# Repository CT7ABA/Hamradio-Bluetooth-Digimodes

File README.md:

# Bluetooth-Digimodes With BT401
Hamradio Digital Modes without Cables.

Don't forget to set up the BT401 to the right communication velocity of your Rig

AT+CT01\r\n for 9600 Baud 

AT+CT02\r\n for 19200 Baud 

AT+CT03\r\n for 38400 Baud

AT+CT04\r\n for 57600 Baud

AT+CT05\r\n for 115200 Baud etc.... take a look at the BT401 manual for more information.

Project still in progress, PCB allready tested. RV1 & RV2 still not the correct values, for the FT-817 both RV are bypassed

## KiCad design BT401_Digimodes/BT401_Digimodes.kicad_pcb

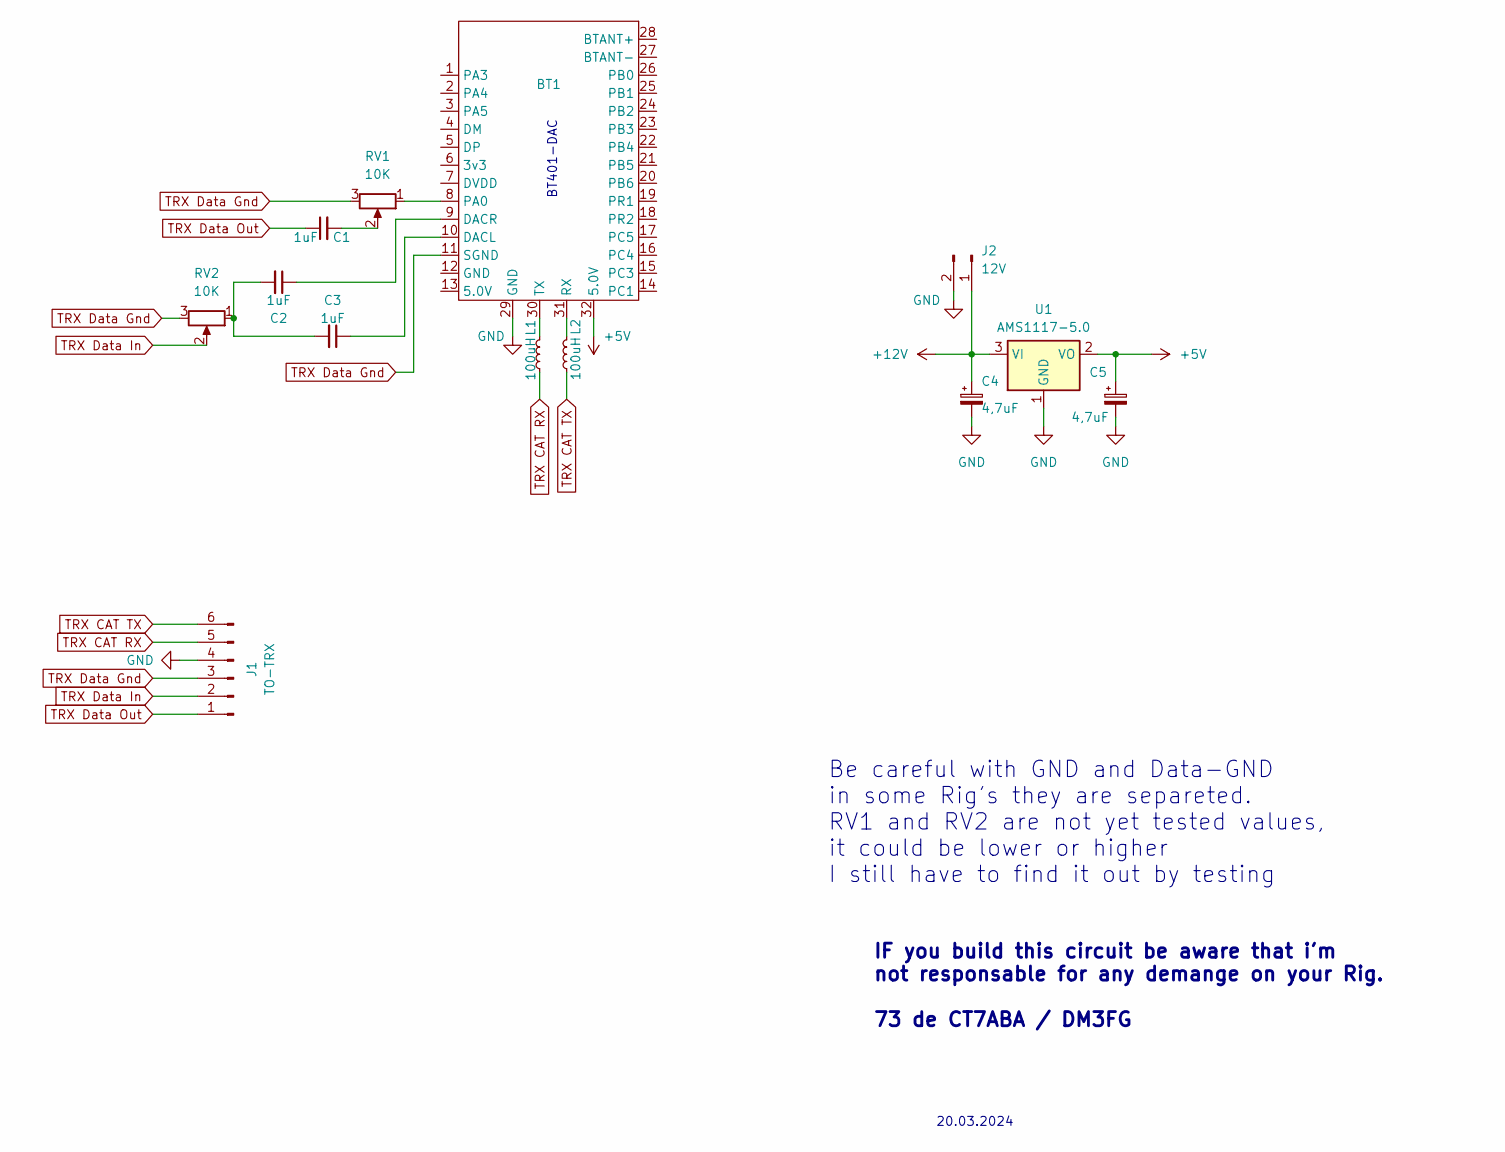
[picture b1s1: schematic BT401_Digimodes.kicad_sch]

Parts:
BT1: BT401
C1, C2, C3: 1uF; C_0805_2012Metric
C4, C5: 4,7uF; CP_Radial_D5.0mm_P2.50mm
J1: TO-TRX; PinHeader_1x06_P2.54mm_Vertical
J2: 12V; PinHeader_1x02_P2.54mm_Vertical
L1, L2: 100uH; R_Axial_DIN0207_L6.3mm_D2.5mm_P2.54mm_Vertical
RV1, RV2: 10K; Potentiometer_Bourns_3266Y_Vertical
U1: AMS1117-5.0; SOT-223-3_TabPin2

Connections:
+5V: BT1.32 (5.0V), C5.1, U1.2 (VO)
+12V: C4.1, J2.1, U1.3 (VI)
GND: BT1.29 (GND), C4.2, C5.2, J1.4, J2.2, U1.1 (GND)
unnamed: BT1.10 (DACL), C3.1
unnamed: BT1.9 (DACR), C2.1
unnamed: BT1.8 (PA0), RV1.1
unnamed: BT1.31 (RX), L2.2
unnamed: BT1.30 (TX), L1.2
unnamed: C1.2, RV1.2
unnamed: C2.2, C3.2, RV2.1
TRX CAT RX: J1.5, L1.1
TRX CAT TX: J1.6, L2.1
TRX Data Gnd: BT1.11 (SGND), J1.3, RV1.3, RV2.3
TRX Data In: J1.2, RV2.2
TRX Data Out: C1.1, J1.1

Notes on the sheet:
IF you build this circuit be aware that i'm not responsable for any demange on your Rig. 73 de CT7ABA / DM3FG
Be careful with GND and Data-GND in some Rig's they are separeted. RV1 and RV2 are not yet tested values, it could be lower or higher I still have to find it out by testing
BT401-DAC
20.03.2024

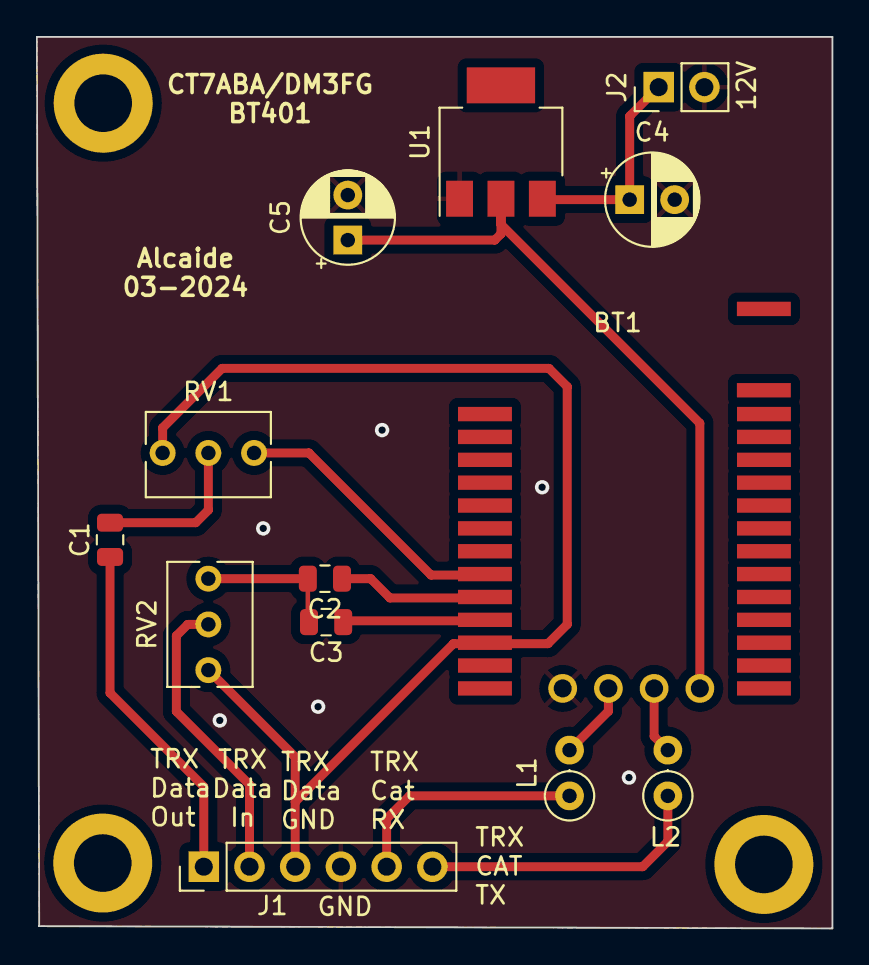
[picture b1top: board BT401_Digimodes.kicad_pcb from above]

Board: 2 copper layers, 44.2 x 49.5 mm, 13 parts (0 on the bottom side), 15 nets.
